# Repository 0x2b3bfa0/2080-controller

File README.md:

# 2080-controller
Controller for Velleman MML24XX LED message boards and MMLXXX/RC IR remotes, originally manufactured by Amplus ([AM03128-H11](http://www.amplus.com.hk/LED_%20AM03128-H13.htm)).

# Usage
The usage is almost the same as the Arduino-IRremote library (as my code is based on that library). I'll try to document the API in the future, but this is not going to happen anytime soon. Now you can simply read my <s>well structured</s> code and figure out the documentation. To find what I've modified from the original library, you can see [this commit](https://github.com/0x2b3bfa0/2080-controller/commit/6ade2232c3832eba8bb211379027a647f3132cfd).

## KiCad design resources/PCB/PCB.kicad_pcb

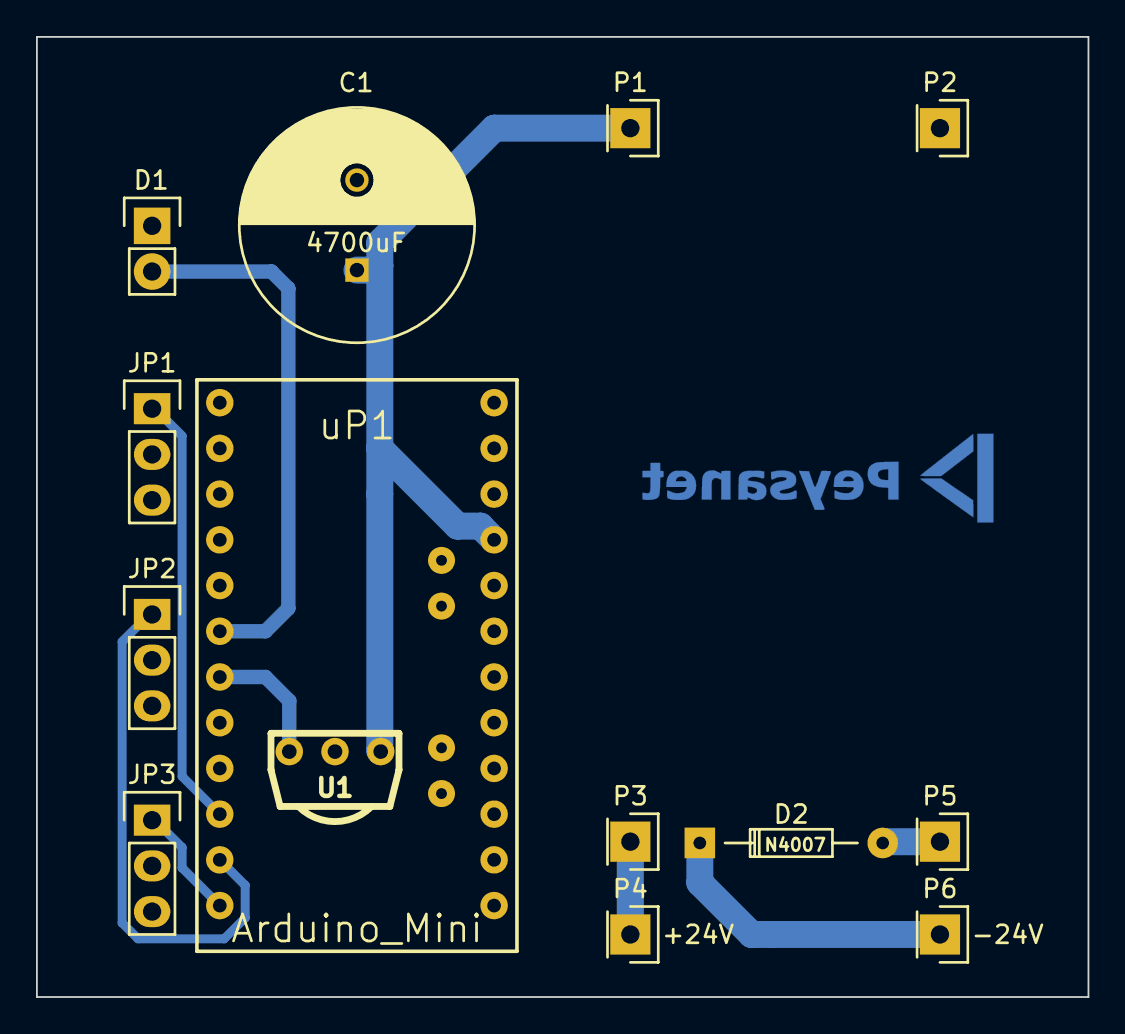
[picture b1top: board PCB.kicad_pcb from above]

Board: 2 copper layers, 58.4 x 53.3 mm, 14 parts (0 on the bottom side), 10 nets.

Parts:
C1: 4700uF; C_Radial_D13_L25_P5
D1: IR; Pin_Header_Straight_1x02
D2: N4007; Diode_DO-35_SOD27_Horizontal_RM10
JP1, JP2, JP3: Jumper_NO_Small; Pin_Header_Straight_1x03
P1: +; Pin_Header_Straight_1x01
P2: -; Pin_Header_Straight_1x01
P3: 24+; Pin_Header_Straight_1x01
P4: +24V; Pin_Header_Straight_1x01
P5: 24-; Pin_Header_Straight_1x01
P6: -24V; Pin_Header_Straight_1x01
U1: TSOP2438
uP1: Arduino_Mini; ArduProMini-6

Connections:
GND: C1.2, D1.1, JP1.2, JP2.2, JP3.2, P2.1, U1.3, uP1.10, uP1.20
IR_RX: U1.1, uP1.13
IR_TX: D1.2, uP1.12
JP1: JP1.1, uP1.16
JP2: JP2.1, uP1.17
JP3: JP3.1, uP1.18
unnamed: D2.1, P6.1
unnamed: D2.2, P5.1
unnamed: P3.1, P4.1
VCC: C1.1, P1.1, U1.2, uP1.22

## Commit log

2016-05-25 Custom library
2016-05-25 Resources
2016-05-29 Velleman product seems to be manufactured by Amplus...
2017-06-14 Delete unneeded files
    However, the commit history is a good backup
2018-09-01 Definitely, I'm silly
2018-09-01 Pull requests are welcome, but not to the point of begging for them.
2018-09-01 Comment rewording
2019-05-08 Some word were misspelled, I fixed that
2019-07-09 Fix typo
2020-10-04 Fix wording
2020-10-04 Compact paragraph
2021-09-25 Create Sjenica1
    Authorized mit meine Account Sjenica1 github.com
